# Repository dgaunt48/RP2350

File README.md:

# RP2350 - Various RP2350 Based Test Projects.

## DRAM_Tester
Code Based On https://github.com/schlae/pico-dram-tester.git
Vastly Cut Down. Just Learning How The RP2350 PIO Works.

## RP2350_LogicV6
50 x 50mm 4 layer self contained version of gusmanb's Logic Analyzer Version 6 Hardware.

## RP2350b_40GPIO
Simple RP2350b dev board with 40 level shifted gpio pins and 3 bit VGA output.

## RTC_MCP951X
Connect a MCP951X Spi Real Time Clock to the Raspberry Pi Pico.

## RTC_MSM6242B
Test the functionality of an obsolete MSM6242B Real Time Clock IC.

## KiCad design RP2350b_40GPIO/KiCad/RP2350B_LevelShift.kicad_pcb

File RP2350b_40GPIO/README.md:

# RP2350b_40GPIO
Simple RP2350b dev board with 40 level shifted gpio pins and 3 bit VGA output.

## Source\SelfTest_40GPIO
Plug a VGA cable in and bridge the left 20 IO pins to the RIGHT 20.
Self test will then perform a simple bi-directional check on all 40 pins, plus check for shorts against the two adjacent pins.
Not exhaustive but will catch most GPIO errors on the board.

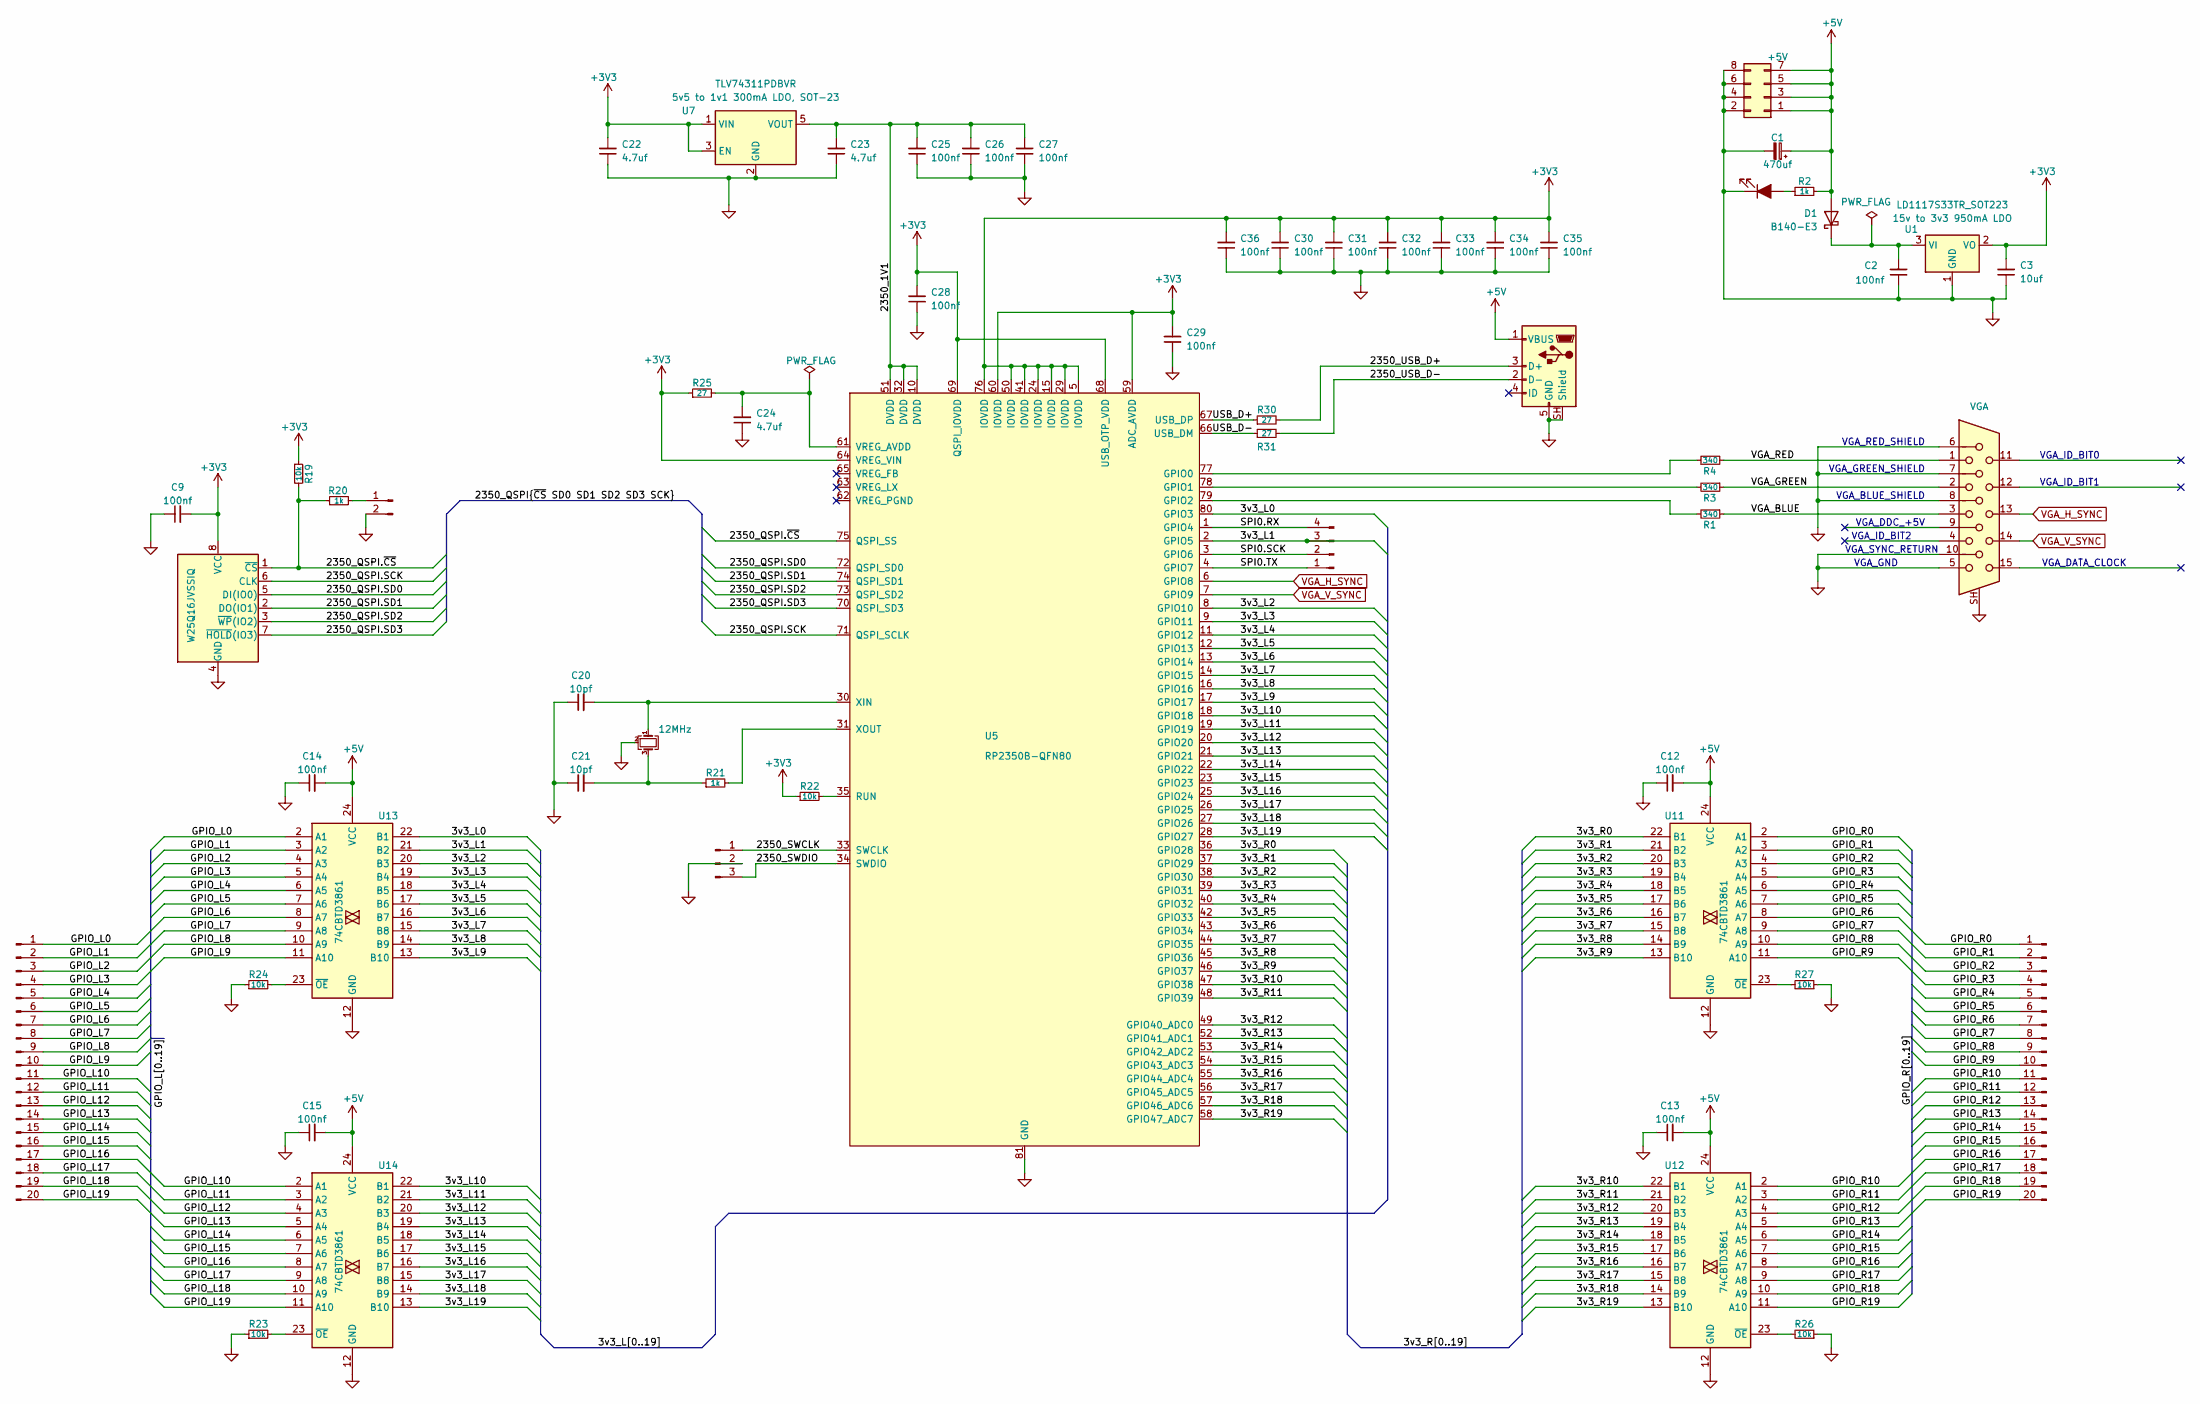
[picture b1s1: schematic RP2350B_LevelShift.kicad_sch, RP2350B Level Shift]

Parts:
C1: 470uf; CP_Radial_D5.0mm_P2.50mm
C2, C9, C12, C13, C14, C15, C25, C26, C27, C28, C29, C30, C31, C32, C33, C34, C35, C36: 100nf; C_0603_1608Metric
C3: 10uf; C_0805_2012Metric
C20, C21: 10pf; C_0603_1608Metric
C22, C23, C24: 4.7uf; C_0805_2012Metric
D1: B140-E3; D_SOD-123
J1: +5V; PinHeader_2x04_P2.54mm_Vertical
J2: Right GPIO; PinHeader_1x20_P2.54mm_Vertical
J3: VGA; 117345301
J4: Left GPIO; PinHeader_1x20_P2.54mm_Vertical
J7: SWD; PinHeader_1x03_P2.54mm_Vertical
J9: BOOT SEL; PinHeader_1x02_P2.54mm_Vertical
J10: SPI; PinHeader_1x04_P2.54mm_Vertical
J13: USB_B_Micro; USB_Micro-B_Amphenol_10103594-0001LF_Horizontal
Power1: POWER; LEDC2012X90N
R1, R3, R4: 340; R_0603_1608Metric
R2, R20, R21: 1k; R_0603_1608Metric
R19, R22, R23, R24, R26, R27: 10k; R_0603_1608Metric
R25, R30, R31: 27; R_0603_1608Metric
U1: LD1117S33TR_SOT223; SOT-223-3_TabPin2; Voltage 3v3
U2: W25Q16JVSSIQ; SOIC-8_5.23x5.23mm_P1.27mm
U5: RP2350B-QFN80; RP2350B_QFN-80_EP_10.573x10.573_Pitch0.4mm
U7: TLV74311PDBVR; SOT-23-5; Voltage 1v1
U11, U12, U13, U14: 74CBTD3861; SSOP-24_3.9x8.7mm_P0.635mm
Y1: 12MHz; Crystal_SMD_SeikoEpson_FA238V-4Pin_3.2x2.5mm

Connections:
+3V3: C3.2, C9.2, C22.2, C28.2, C29.2, C30.2, C31.2, C32.2, C33.2, C34.2, C35.2, C36.2, R19.1, R22.1, R25.1, U1.2 (VO), U2.8 (VCC), U5.5 (IOVDD), U5.15 (IOVDD), U5.24 (IOVDD), U5.29 (IOVDD), U5.41 (IOVDD), U5.50 (IOVDD), U5.59 (ADC_AVDD), U5.60 (IOVDD), U5.64 (VREG_VIN), U5.68 (USB_OTP_VDD), U5.69 (QSPI_IOVDD), U5.76 (IOVDD), U7.1 (VIN), U7.3 (EN)
+5V: C1.1, C12.2, C13.2, C14.2, C15.2, D1.2 (A), J1.1, J1.3, J1.5, J1.7, J13.1 (VBUS), R2.2, U11.24 (VCC), U12.24 (VCC), U13.24 (VCC), U14.24 (VCC)
/3v3_L0: U5.80 (GPIO3), U13.22 (B1)
/3v3_L1: J10.3, U5.2 (GPIO5), U13.21 (B2)
/3v3_L2: U5.8 (GPIO10), U13.20 (B3)
/3v3_L3: U5.9 (GPIO11), U13.19 (B4)
/3v3_L4: U5.11 (GPIO12), U13.18 (B5)
/3v3_L5: U5.12 (GPIO13), U13.17 (B6)
/3v3_L6: U5.13 (GPIO14), U13.16 (B7)
/3v3_L7: U5.14 (GPIO15), U13.15 (B8)
/3v3_L8: U5.16 (GPIO16), U13.14 (B9)
/3v3_L9: U5.17 (GPIO17), U13.13 (B10)
/3v3_L10: U5.18 (GPIO18), U14.22 (B1)
/3v3_L11: U5.19 (GPIO19), U14.21 (B2)
/3v3_L12: U5.20 (GPIO20), U14.20 (B3)
/3v3_L13: U5.21 (GPIO21), U14.19 (B4)
/3v3_L14: U5.22 (GPIO22), U14.18 (B5)
/3v3_L15: U5.23 (GPIO23), U14.17 (B6)
/3v3_L16: U5.25 (GPIO24), U14.16 (B7)
/3v3_L17: U5.26 (GPIO25), U14.15 (B8)
/3v3_L18: U5.27 (GPIO26), U14.14 (B9)
/3v3_L19: U5.28 (GPIO27), U14.13 (B10)
/3v3_R0: U5.36 (GPIO28), U11.22 (B1)
/3v3_R1: U5.37 (GPIO29), U11.21 (B2)
/3v3_R2: U5.38 (GPIO30), U11.20 (B3)
/3v3_R3: U5.39 (GPIO31), U11.19 (B4)
/3v3_R4: U5.40 (GPIO32), U11.18 (B5)
/3v3_R5: U5.42 (GPIO33), U11.17 (B6)
/3v3_R6: U5.43 (GPIO34), U11.16 (B7)
/3v3_R7: U5.44 (GPIO35), U11.15 (B8)
/3v3_R8: U5.45 (GPIO36), U11.14 (B9)
/3v3_R9: U5.46 (GPIO37), U11.13 (B10)
/3v3_R10: U5.47 (GPIO38), U12.22 (B1)
/3v3_R11: U5.48 (GPIO39), U12.21 (B2)
/3v3_R12: U5.49 (GPIO40_ADC0), U12.20 (B3)
/3v3_R13: U5.52 (GPIO41_ADC1), U12.19 (B4)
/3v3_R14: U5.53 (GPIO42_ADC2), U12.18 (B5)
/3v3_R15: U5.54 (GPIO43_ADC3), U12.17 (B6)
/3v3_R16: U5.55 (GPIO44_ADC4), U12.16 (B7)
/3v3_R17: U5.56 (GPIO45_ADC5), U12.15 (B8)
/3v3_R18: U5.57 (GPIO46_ADC6), U12.14 (B9)
/3v3_R19: U5.58 (GPIO47_ADC7), U12.13 (B10)
/2350_1V1: C23.2, C25.2, C26.2, C27.2, U5.10 (DVDD), U5.32 (DVDD), U5.51 (DVDD), U7.5 (VOUT)
/2350_QSPI.SCK: U2.6 (CLK), U5.71 (QSPI_SCLK)
/2350_QSPI.SD0: U2.5 (DI(IO0)), U5.72 (QSPI_SD0)
/2350_QSPI.SD1: U2.2 (DO(IO1)), U5.74 (QSPI_SD1)
/2350_QSPI.SD2: U2.3 (~WP(IO2)), U5.73 (QSPI_SD2)
/2350_QSPI.SD3: U2.7 (~HOLD(IO3)), U5.70 (QSPI_SD3)
/2350_QSPI.~CS: R19.2, R20.1, U2.1 (~CS), U5.75 (QSPI_SS)
/2350_SWCLK: J7.1, U5.33 (SWCLK)
/2350_SWDIO: J7.3, U5.34 (SWDIO)
/2350_USB_D+: J13.3 (D+), R30.2
/2350_USB_D-: J13.2 (D-), R31.2
/GPIO_L0: J4.1, U13.2 (A1)
/GPIO_L1: J4.2, U13.3 (A2)
/GPIO_L2: J4.3, U13.4 (A3)
/GPIO_L3: J4.4, U13.5 (A4)
/GPIO_L4: J4.5, U13.6 (A5)
/GPIO_L5: J4.6, U13.7 (A6)
/GPIO_L6: J4.7, U13.8 (A7)
/GPIO_L7: J4.8, U13.9 (A8)
/GPIO_L8: J4.9, U13.10 (A9)
/GPIO_L9: J4.10, U13.11 (A10)
/GPIO_L10: J4.11, U14.2 (A1)
/GPIO_L11: J4.12, U14.3 (A2)
/GPIO_L12: J4.13, U14.4 (A3)
/GPIO_L13: J4.14, U14.5 (A4)
/GPIO_L14: J4.15, U14.6 (A5)
/GPIO_L15: J4.16, U14.7 (A6)
/GPIO_L16: J4.17, U14.8 (A7)
/GPIO_L17: J4.18, U14.9 (A8)
/GPIO_L18: J4.19, U14.10 (A9)
/GPIO_L19: J4.20, U14.11 (A10)
/GPIO_R0: J2.1, U11.2 (A1)
/GPIO_R1: J2.2, U11.3 (A2)
/GPIO_R2: J2.3, U11.4 (A3)
/GPIO_R3: J2.4, U11.5 (A4)
/GPIO_R4: J2.5, U11.6 (A5)
/GPIO_R5: J2.6, U11.7 (A6)
/GPIO_R6: J2.7, U11.8 (A7)
/GPIO_R7: J2.8, U11.9 (A8)
/GPIO_R8: J2.9, U11.10 (A9)
/GPIO_R9: J2.10, U11.11 (A10)
/GPIO_R10: J2.11, U12.2 (A1)
/GPIO_R11: J2.12, U12.3 (A2)
/GPIO_R12: J2.13, U12.4 (A3)
/GPIO_R13: J2.14, U12.5 (A4)
/GPIO_R14: J2.15, U12.6 (A5)
/GPIO_R15: J2.16, U12.7 (A6)
/GPIO_R16: J2.17, U12.8 (A7)
/GPIO_R17: J2.18, U12.9 (A8)
/GPIO_R18: J2.19, U12.10 (A9)
/GPIO_R19: J2.20, U12.11 (A10)
/SPI0.RX: J10.4, U5.1 (GPIO4)
/SPI0.SCK: J10.2, U5.3 (GPIO6)
/SPI0.TX: J10.1, U5.4 (GPIO7)
/USB_D+: R30.1, U5.67 (USB_DP)
/USB_D-: R31.1, U5.66 (USB_DM)
/VGA_BLUE: J3.3, R1.1
/VGA_GREEN: J3.2, R3.1
/VGA_RED: J3.1, R4.1
GND: C1.2, C2.1, C3.1, C9.1, C12.1, C13.1, C14.1, C15.1, C20.1, C21.1, C22.1, C23.1, C24.1, C25.1, C26.1, C27.1, C28.1, C29.1, C30.1, C31.1, C32.1, C33.1, C34.1, C35.1, C36.1, J1.2, J1.4, J1.6, J1.8, J3.5, J3.6, J3.7, J3.8, J3.10, J3.SH, J7.2, J9.2, J13.5 (GND), J13.SH (Shield), Power1.1 (K), R23.1, R24.1, R26.1, R27.1, U1.1 (GND), U2.4 (GND), U5.81 (GND), U7.2 (GND), U11.12 (GND), U12.12 (GND), U13.12 (GND), U14.12 (GND), Y1.2 (G), Y1.4 (G)
unnamed: C21.2, R21.1, Y1.3
unnamed: C2.2, D1.1 (K), U1.3 (VI)
unnamed: J9.1, R20.2
unnamed: Power1.2 (A), R2.1
unnamed: R4.2, U5.77 (GPIO0)
unnamed: R3.2, U5.78 (GPIO1)
unnamed: R1.2, U5.79 (GPIO2)
unnamed: R22.2, U5.35 (RUN)
unnamed: C24.2, R25.2, U5.61 (VREG_AVDD)
unnamed: C20.2, U5.30 (XIN), Y1.1
unnamed: R21.2, U5.31 (XOUT)
unnamed: R27.2, U11.23 (~OE)
unnamed: R26.2, U12.23 (~OE)
unnamed: R24.2, U13.23 (~OE)
unnamed: R23.2, U14.23 (~OE)
VGA_H_SYNC: J3.13, U5.6 (GPIO8)
VGA_V_SYNC: J3.14, U5.7 (GPIO9)

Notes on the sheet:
VGA_ID_BIT2
VGA_ID_BIT1
VGA_BLUE_SHIELD
VGA_ID_BIT0
VGA_DATA_CLOCK
VGA_RED_SHIELD
VGA_DDC_+5V
VGA_SYNC_RETURN
VGA_GND
VGA_GREEN_SHIELD

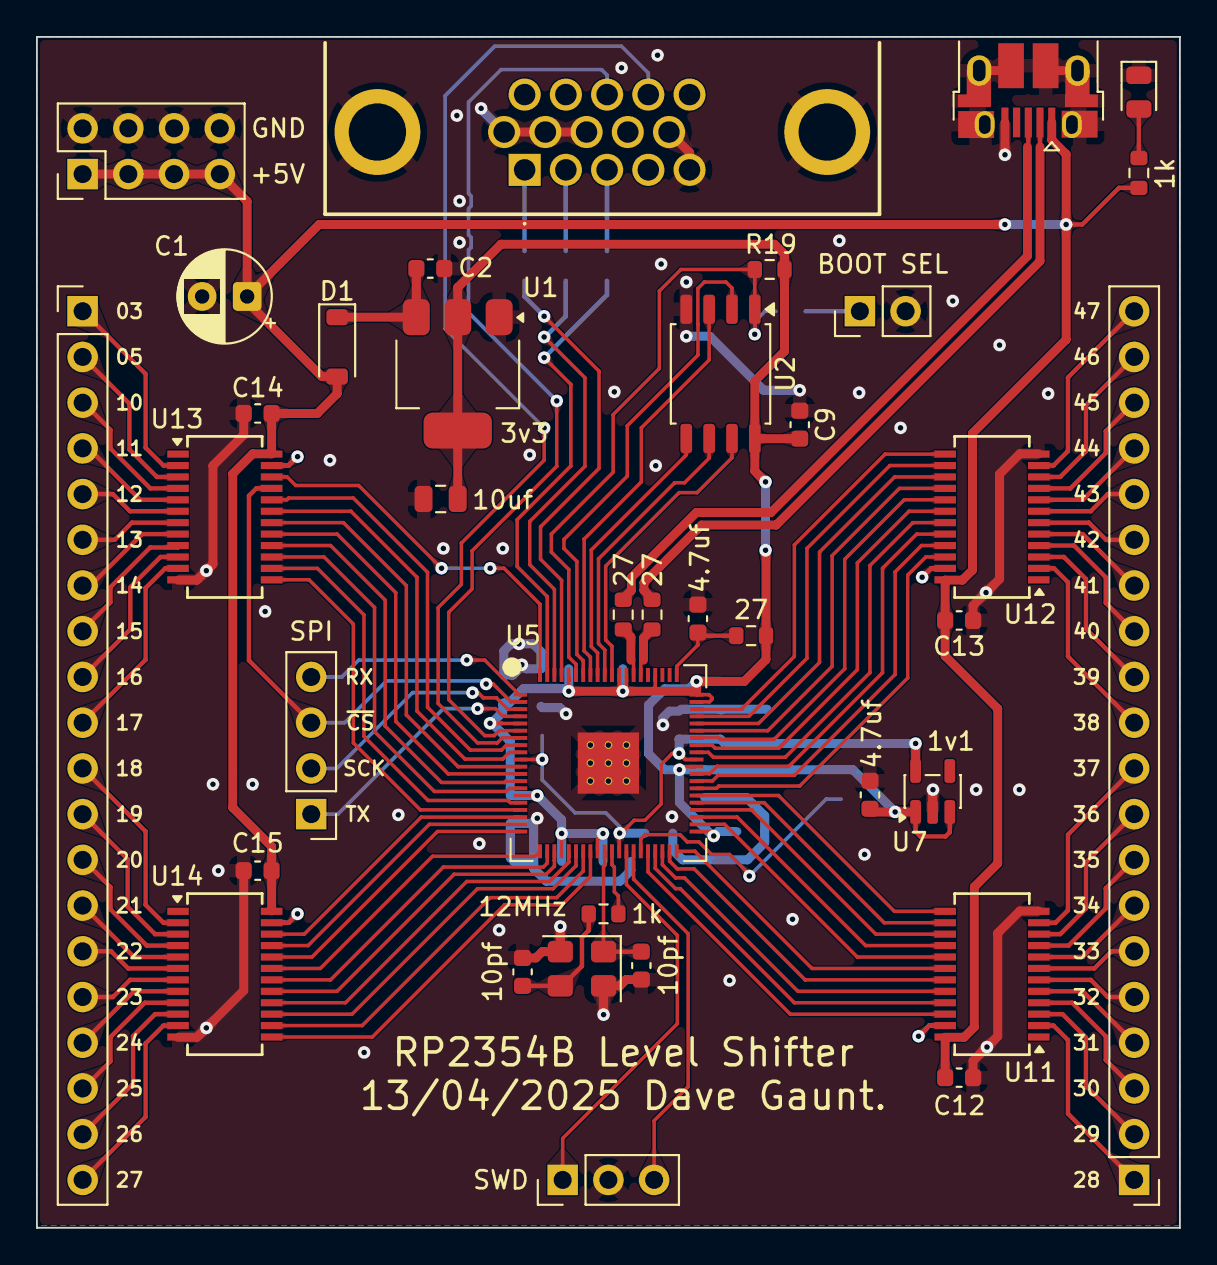
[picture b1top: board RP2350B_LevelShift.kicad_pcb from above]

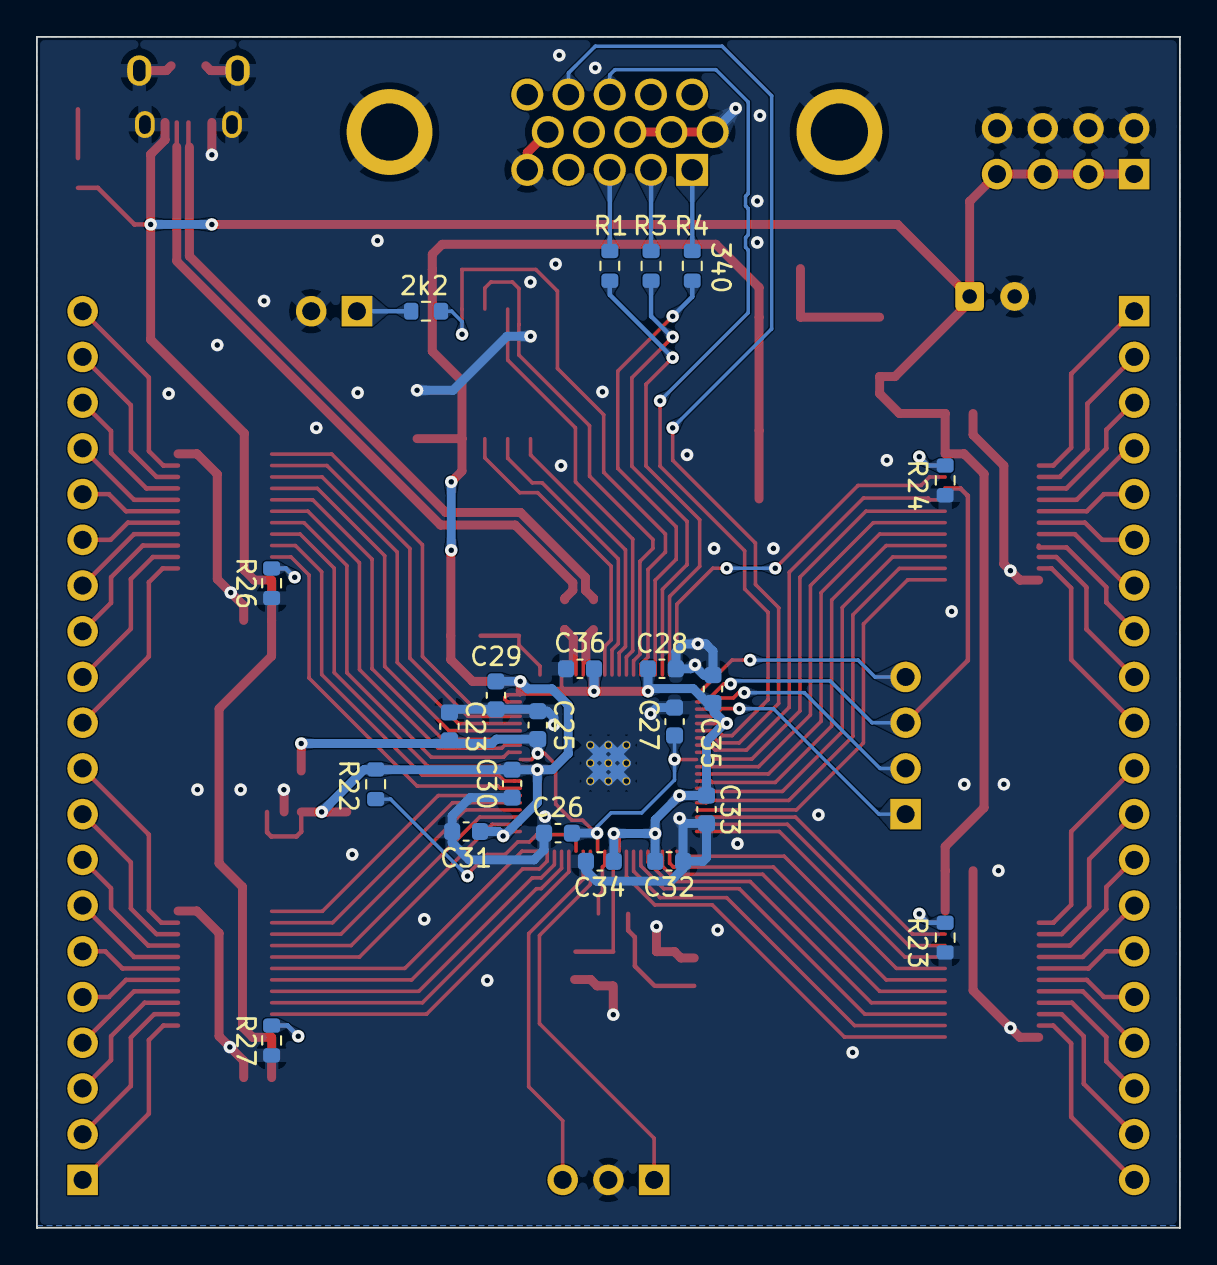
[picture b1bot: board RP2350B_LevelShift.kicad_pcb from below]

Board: 2 copper layers, 63.5 x 66.2 mm, 59 parts (22 on the bottom side), 119 nets.

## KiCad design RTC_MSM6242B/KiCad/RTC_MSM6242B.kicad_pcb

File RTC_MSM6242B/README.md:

# MSM6242B Real Time Clock

Project to test the functionality of an obsolete MSM6242B Real Time Clock IC with the 2350.

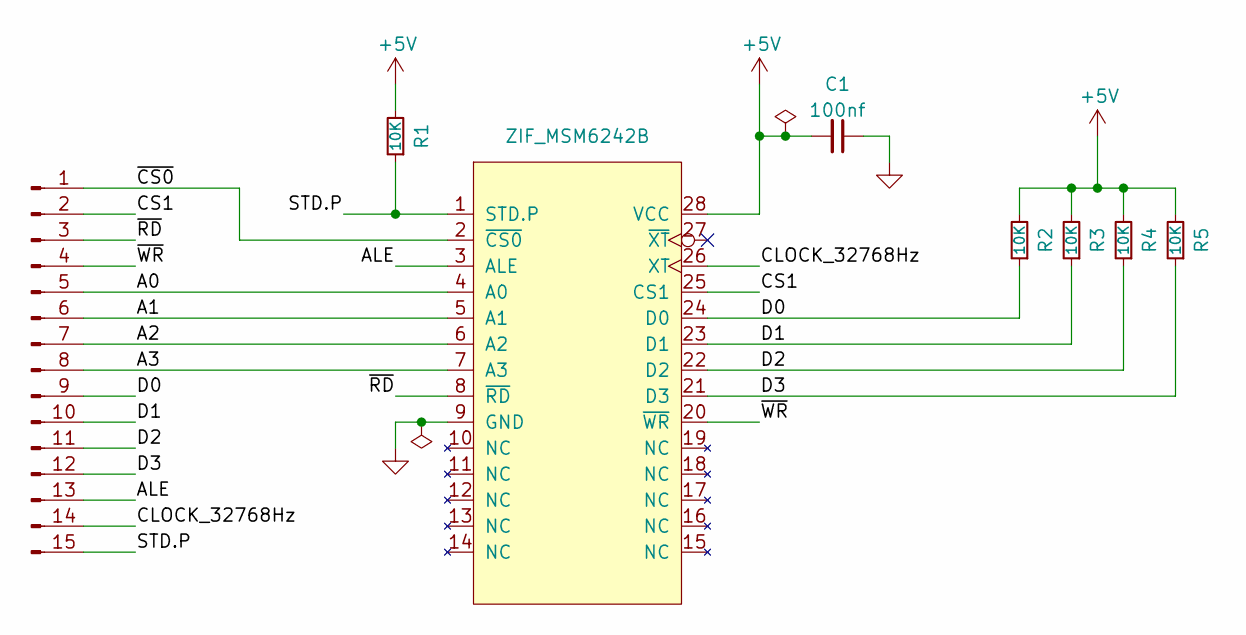
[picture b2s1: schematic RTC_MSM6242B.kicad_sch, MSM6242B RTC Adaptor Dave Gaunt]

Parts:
C1: 100nf; C_0603_1608Metric
J1: PinHeader_1x15_P2.54mm_Vertical
R1, R2, R3, R4, R5: 10K; R_0603_1608Metric
U1: ZIF_MSM6242B; ZIF-28_W11.9mm_W12.7mm_W15.24mm_W17.78mm_W18.5mm_3M_228-127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

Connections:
+5V: C1.2, R1.2, R2.2, R3.2, R4.2, R5.2, U1.28 (VCC)
/A0: J1.5, U1.4 (A0)
/A1: J1.6, U1.5 (A1)
/A2: J1.7, U1.6 (A2)
/A3: J1.8, U1.7 (A3)
/ALE: J1.13, U1.3 (ALE)
/CLOCK_32768Hz: J1.14, U1.26 (XT)
/CS1: J1.2, U1.25 (CS1)
/D0: J1.9, R2.1, U1.24 (D0)
/D1: J1.10, R3.1, U1.23 (D1)
/D2: J1.11, R4.1, U1.22 (D2)
/D3: J1.12, R5.1, U1.21 (D3)
/STD.P: J1.15, R1.1, U1.1 (STD.P)
/~CS0: J1.1, U1.2 (~CS0)
/~RD: J1.3, U1.8 (~RD)
/~WR: J1.4, U1.20 (~WR)
GND: C1.1, U1.9 (GND)

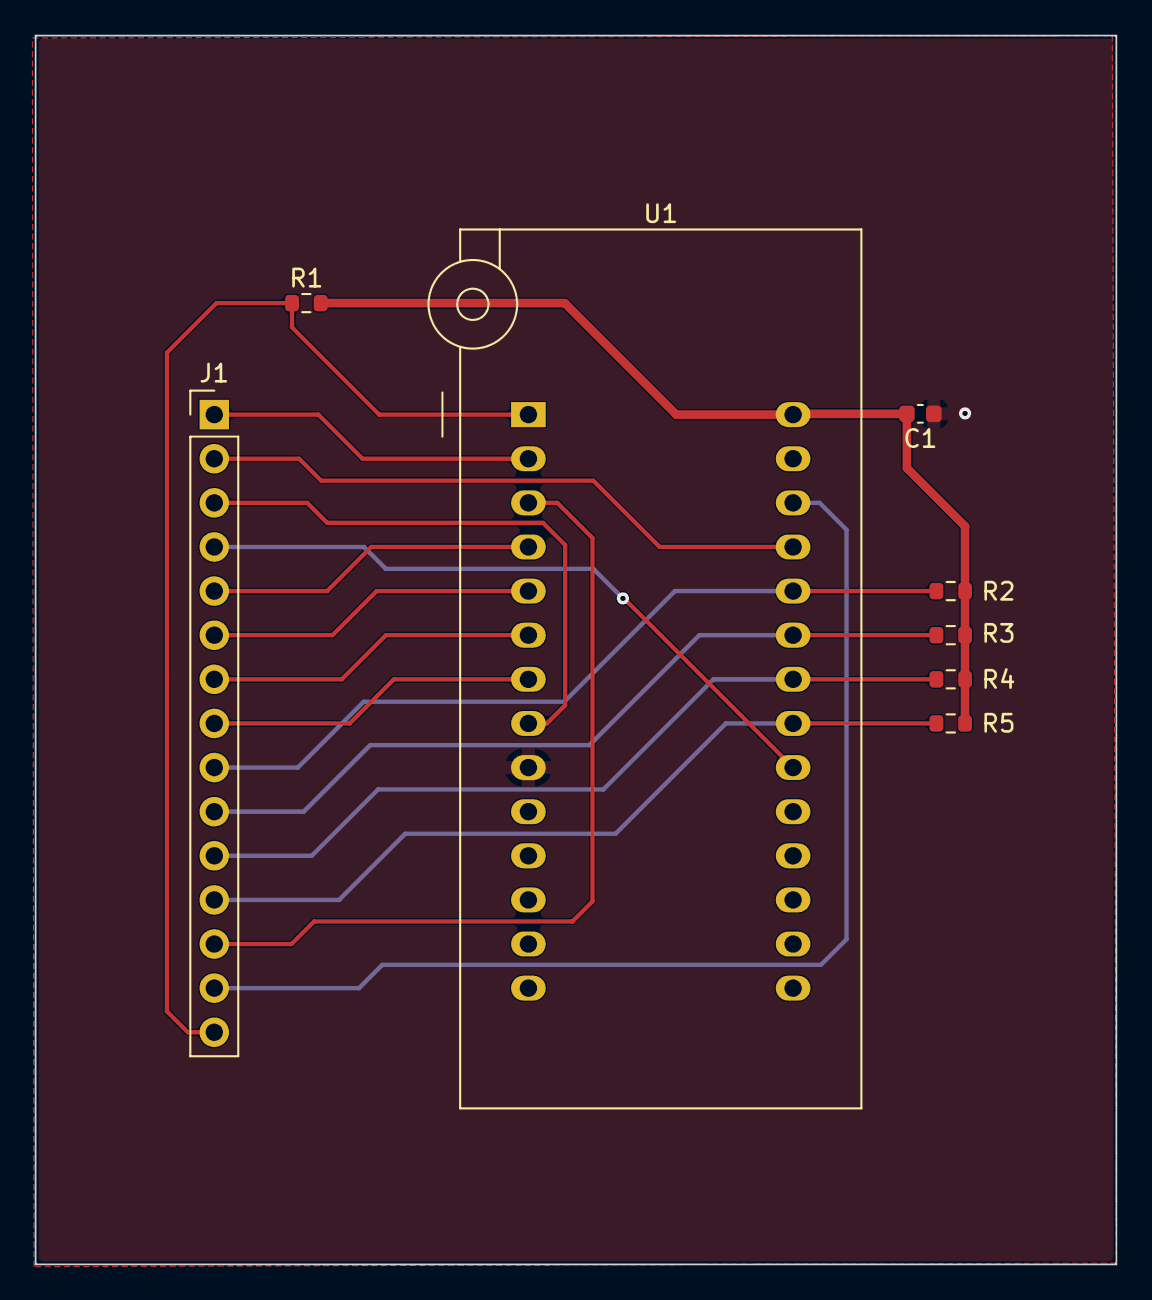
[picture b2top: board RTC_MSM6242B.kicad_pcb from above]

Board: 2 copper layers, 62.2 x 70.7 mm, 8 parts (0 on the bottom side), 17 nets.

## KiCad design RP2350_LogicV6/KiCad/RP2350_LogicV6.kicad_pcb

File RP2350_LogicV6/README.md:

# RP2350_LogicV6

50 x 50mm 4 layer self contained version of gusmanb's Logic Analyzer Hardware.

https://github.com/gusmanb/logicanalyzer.git

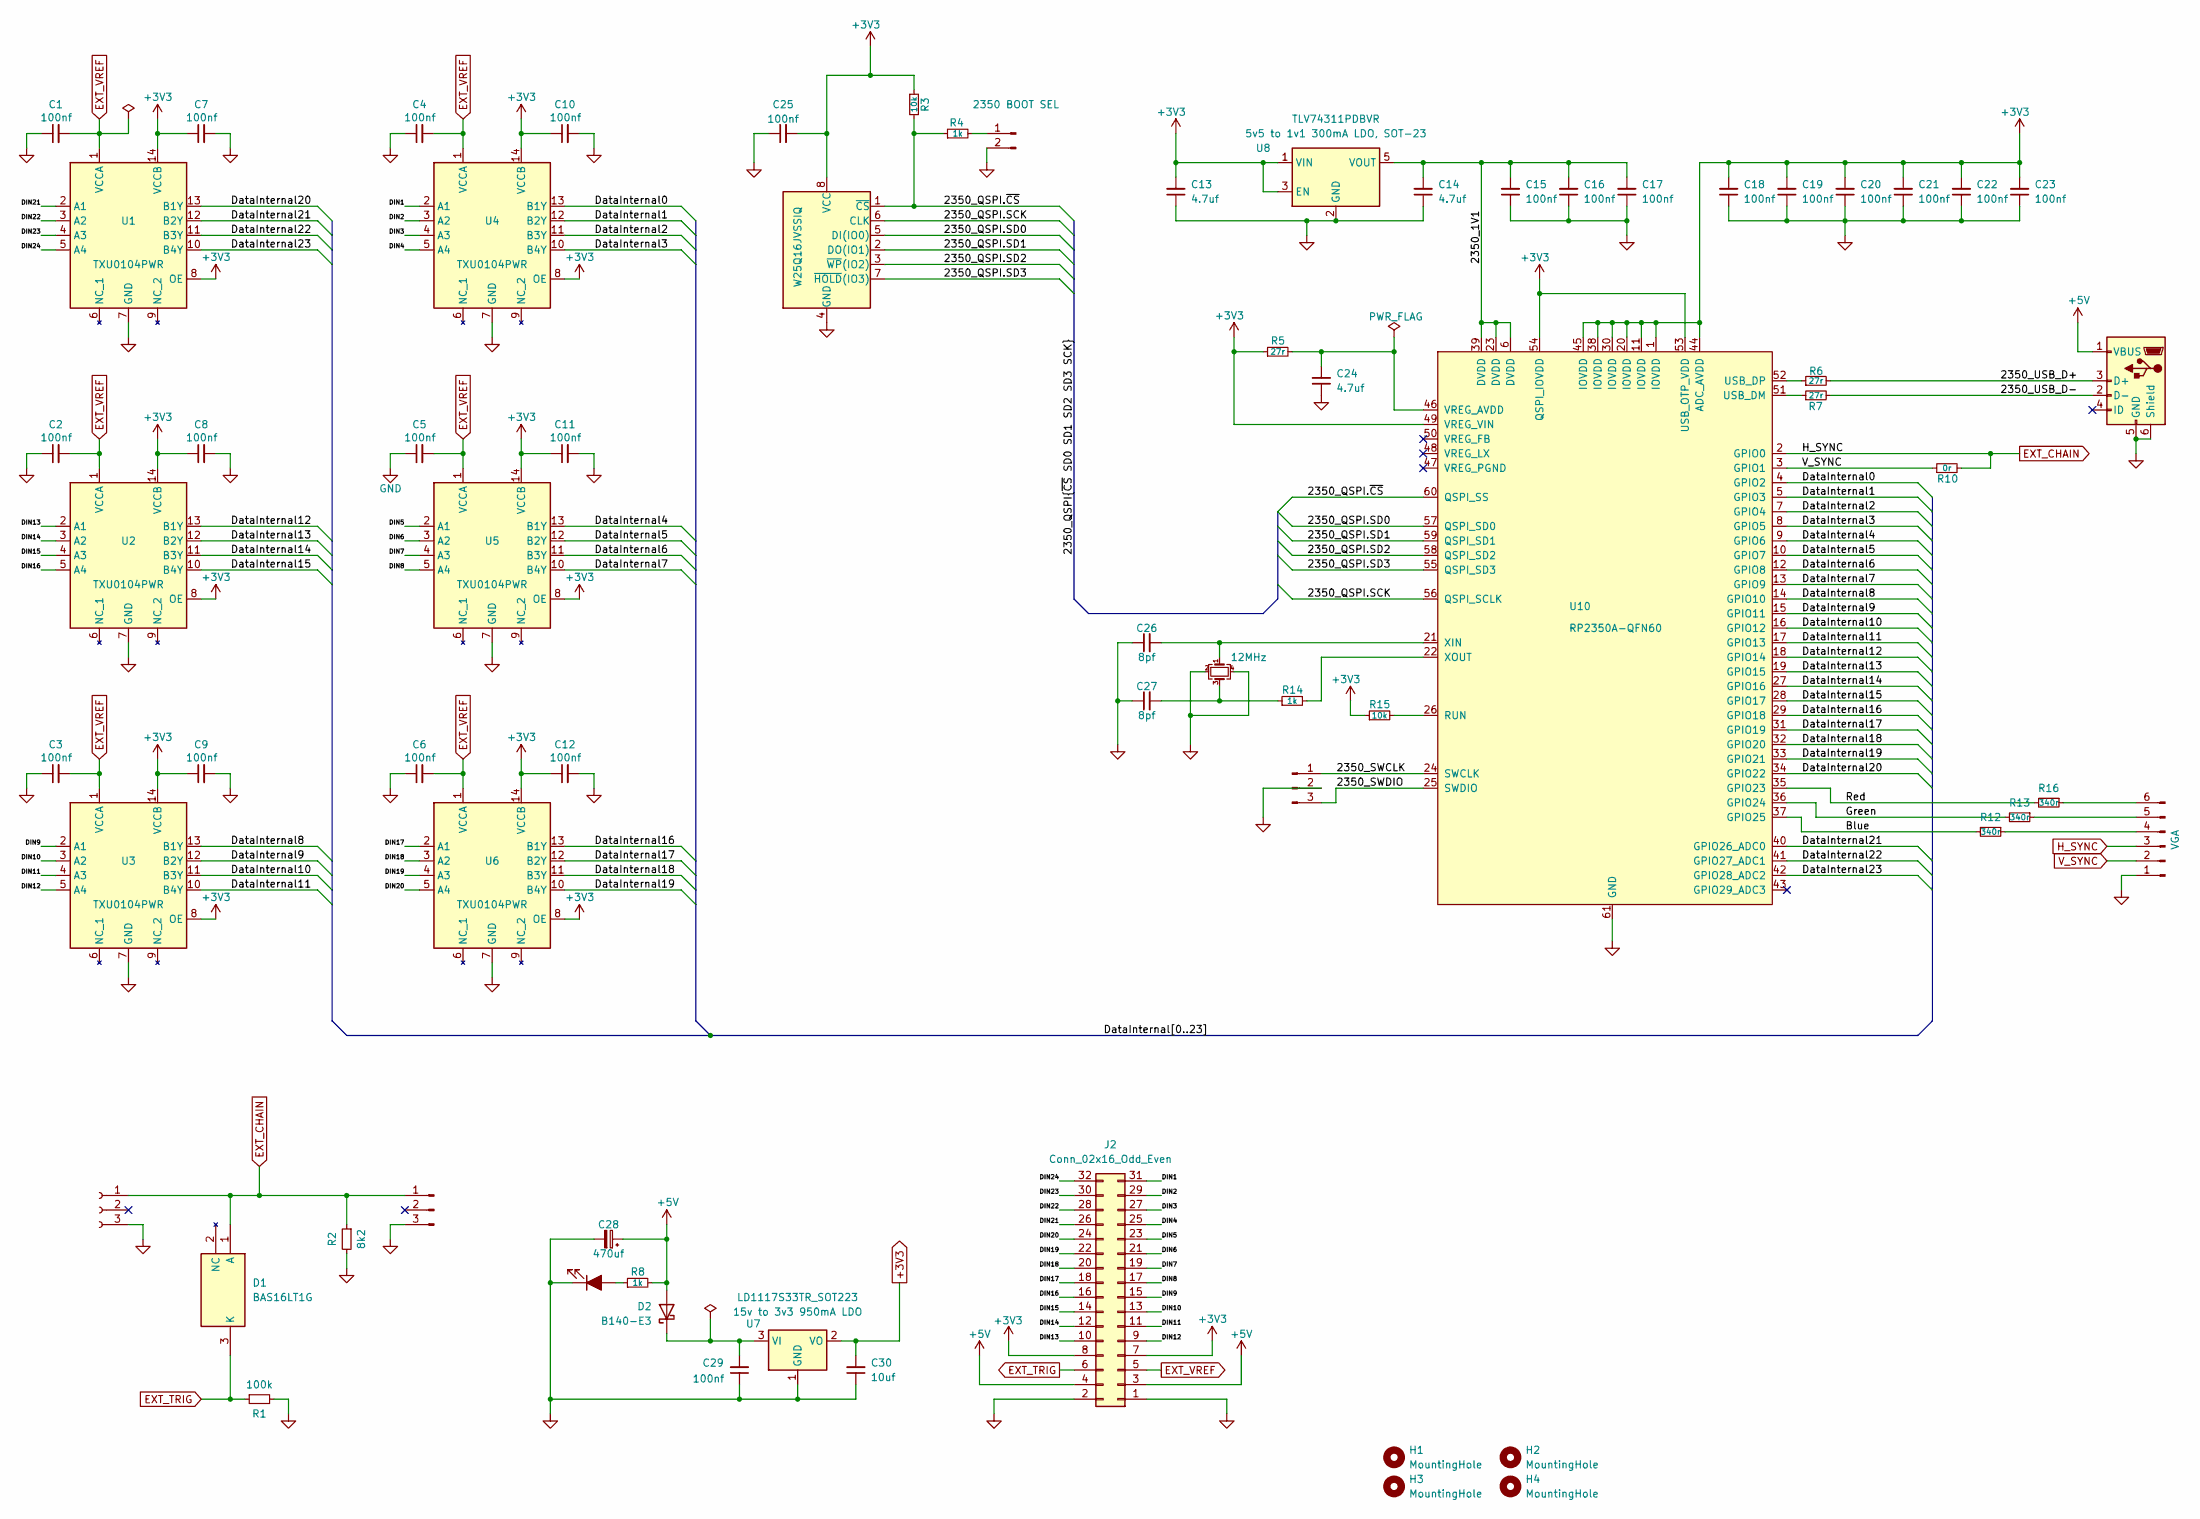
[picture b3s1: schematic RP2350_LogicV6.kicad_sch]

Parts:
C1, C2, C3, C4, C5, C6, C7, C8, C9, C10, C11, C12, C15, C16, C17, C18, C19, C20, C21, C22, C23, C25, C29: 100nf; C_0603_1608Metric
C13, C14, C24: 4.7uf; C_0805_2012Metric
C26, C27: 8pf; C_0603_1608Metric
C28: 470uf; CP_Radial_D5.0mm_P2.50mm
C30: 10uf; C_0805_2012Metric
D1: BAS16LT1G; SOT96P237X111-3N; Mouser Part Number 863-BAS16LT1G
D2: B140-E3; D_SOD-123
H1, H2, H3, H4: MountingHole; MountingHole_2.5mm
J2: Conn_02x16_Odd_Even; PinHeader_2x16_P2.54mm_Horizontal
J3: SWD; PinSocket_1x03_P2.54mm_Horizontal
J4: USB_B_Micro; USB_Micro-B_Amphenol_10103594-0001LF_Horizontal
J5: 2350 BOOT SEL; PinHeader_1x02_P2.54mm_Vertical
J6: SWD; PinHeader_1x03_P2.54mm_Vertical
J7: SWD; PinHeader_1x03_P2.54mm_Horizontal
J9: VGA; PinHeader_1x06_P2.54mm_Vertical
Power1: POWER; LEDC2012X90N
R1: 100k; R_0603_1608Metric
R2: 8k2; R_0603_1608Metric
R3, R15: 10k; R_0603_1608Metric
R4, R8, R14: 1k; R_0603_1608Metric
R5, R6, R7: 27r; R_0603_1608Metric
R10: 0r; R_0603_1608Metric
R12, R13, R16: 340r; R_0603_1608Metric
U1, U2, U3, U4, U5, U6: TXU0104PWR; SOP65P640X120-14N; Mouser Part Number 595-TXU0104PWR
U7: LD1117S33TR_SOT223; SOT-223-3_TabPin2; Voltage 3v3
U8: TLV74311PDBVR; SOT-23-5; Voltage 1v1
U9: W25Q16JVSSIQ; SOIC-8_5.23x5.23mm_P1.27mm
U10: RP2350A-QFN60; RP2350A_QFN-60_EP_7.75x7.75_Pitch0.4mm
Y1: 12MHz; Crystal_SMD_SeikoEpson_FA238V-4Pin_3.2x2.5mm

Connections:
+3V3: C7.1, C8.1, C9.1, C10.1, C11.1, C12.1, C13.2, C18.2, C19.2, C20.2, C21.2, C22.2, C23.2, C25.2, C30.2, J2.7, J2.8, R3.1, R5.1, R15.1, U1.8 (OE), U1.14 (VCCB), U2.8 (OE), U2.14 (VCCB), U3.8 (OE), U3.14 (VCCB), U4.8 (OE), U4.14 (VCCB), U5.8 (OE), U5.14 (VCCB), U6.8 (OE), U6.14 (VCCB), U7.2 (VO), U8.1 (VIN), U8.3 (EN), U9.8 (VCC), U10.1 (IOVDD), U10.11 (IOVDD), U10.20 (IOVDD), U10.30 (IOVDD), U10.38 (IOVDD), U10.44 (ADC_AVDD), U10.45 (IOVDD), U10.49 (VREG_VIN), U10.53 (USB_OTP_VDD), U10.54 (QSPI_IOVDD)
+5V: C28.1, D2.2 (A), J2.3, J2.4, J4.1 (VBUS), R8.2
/2350_1V1: C14.2, C15.2, C16.2, C17.2, U8.5 (VOUT), U10.6 (DVDD), U10.23 (DVDD), U10.39 (DVDD)
/2350_QSPI.SCK: U9.6 (CLK), U10.56 (QSPI_SCLK)
/2350_QSPI.SD0: U9.5 (DI(IO0)), U10.57 (QSPI_SD0)
/2350_QSPI.SD1: U9.2 (DO(IO1)), U10.59 (QSPI_SD1)
/2350_QSPI.SD2: U9.3 (~WP(IO2)), U10.58 (QSPI_SD2)
/2350_QSPI.SD3: U9.7 (~HOLD(IO3)), U10.55 (QSPI_SD3)
/2350_QSPI.~CS: R3.2, R4.1, U9.1 (~CS), U10.60 (QSPI_SS)
/2350_SWCLK: J6.1, U10.24 (SWCLK)
/2350_SWDIO: J6.3, U10.25 (SWDIO)
/2350_USB_D+: J4.3 (D+), R6.2
/2350_USB_D-: J4.2 (D-), R7.2
/Blue: R12.2, U10.37 (GPIO25)
/DIN1: J2.31, U4.2 (A1)
/DIN2: J2.29, U4.3 (A2)
/DIN3: J2.27, U4.4 (A3)
/DIN4: J2.25, U4.5 (A4)
/DIN5: J2.23, U5.2 (A1)
/DIN6: J2.21, U5.3 (A2)
/DIN7: J2.19, U5.4 (A3)
/DIN8: J2.17, U5.5 (A4)
/DIN9: J2.15, U3.2 (A1)
/DIN10: J2.13, U3.3 (A2)
/DIN11: J2.11, U3.4 (A3)
/DIN12: J2.9, U3.5 (A4)
/DIN13: J2.10, U2.2 (A1)
/DIN14: J2.12, U2.3 (A2)
/DIN15: J2.14, U2.4 (A3)
/DIN16: J2.16, U2.5 (A4)
/DIN17: J2.18, U6.2 (A1)
/DIN18: J2.20, U6.3 (A2)
/DIN19: J2.22, U6.4 (A3)
/DIN20: J2.24, U6.5 (A4)
/DIN21: J2.26, U1.2 (A1)
/DIN22: J2.28, U1.3 (A2)
/DIN23: J2.30, U1.4 (A3)
/DIN24: J2.32, U1.5 (A4)
/DataInternal0: U4.13 (B1Y), U10.4 (GPIO2)
/DataInternal1: U4.12 (B2Y), U10.5 (GPIO3)
/DataInternal2: U4.11 (B3Y), U10.7 (GPIO4)
/DataInternal3: U4.10 (B4Y), U10.8 (GPIO5)
/DataInternal4: U5.13 (B1Y), U10.9 (GPIO6)
/DataInternal5: U5.12 (B2Y), U10.10 (GPIO7)
/DataInternal6: U5.11 (B3Y), U10.12 (GPIO8)
/DataInternal7: U5.10 (B4Y), U10.13 (GPIO9)
/DataInternal8: U3.13 (B1Y), U10.14 (GPIO10)
/DataInternal9: U3.12 (B2Y), U10.15 (GPIO11)
/DataInternal10: U3.11 (B3Y), U10.16 (GPIO12)
/DataInternal11: U3.10 (B4Y), U10.17 (GPIO13)
/DataInternal12: U2.13 (B1Y), U10.18 (GPIO14)
/DataInternal13: U2.12 (B2Y), U10.19 (GPIO15)
/DataInternal14: U2.11 (B3Y), U10.27 (GPIO16)
/DataInternal15: U2.10 (B4Y), U10.28 (GPIO17)
/DataInternal16: U6.13 (B1Y), U10.29 (GPIO18)
/DataInternal17: U6.12 (B2Y), U10.31 (GPIO19)
/DataInternal18: U6.11 (B3Y), U10.32 (GPIO20)
/DataInternal19: U6.10 (B4Y), U10.33 (GPIO21)
/DataInternal20: U1.13 (B1Y), U10.34 (GPIO22)
/DataInternal21: U1.12 (B2Y), U10.40 (GPIO26_ADC0)
/DataInternal22: U1.11 (B3Y), U10.41 (GPIO27_ADC1)
/DataInternal23: U1.10 (B4Y), U10.42 (GPIO28_ADC2)
/Green: R13.2, U10.36 (GPIO24)
/Red: R16.2, U10.35 (GPIO23)
/V_SYNC: J9.2, R10.1, U10.3 (GPIO1)
EXT_TRIG: D1.3 (K), J2.6, R1.1
EXT_VREF: C1.2, C2.2, C3.2, C4.2, C5.2, C6.2, J2.5, U1.1 (VCCA), U2.1 (VCCA), U3.1 (VCCA), U4.1 (VCCA), U5.1 (VCCA), U6.1 (VCCA)
GND: C1.1, C2.1, C3.1, C4.1, C5.1, C6.1, C7.2, C8.2, C9.2, C10.2, C11.2, C12.2, C13.1, C14.1, C15.1, C16.1, C17.1, C18.1, C19.1, C20.1, C21.1, C22.1, C23.1, C24.1, C25.1, C26.1, C27.1, C28.2, C29.1, C30.1, J2.1, J2.2, J3.3, J4.5 (GND), J4.6 (Shield), J4.SH (Shield), J5.2, J6.2, J7.3, J9.1, Power1.1 (K), R1.2, R2.2, U1.7 (GND), U2.7 (GND), U3.7 (GND), U4.7 (GND), U5.7 (GND), U6.7 (GND), U7.1 (GND), U8.2 (GND), U9.4 (GND), U10.61 (GND), Y1.2 (G), Y1.4 (G)
unnamed: C27.2, R14.1, Y1.3
unnamed: C29.2, D2.1 (K), U7.3 (VI)
unnamed: J5.1, R4.2
unnamed: J9.4, R12.1
unnamed: J9.5, R13.1
unnamed: J9.6, R16.1
unnamed: Power1.2 (A), R8.1
unnamed: R15.2, U10.26 (RUN)
unnamed: R7.1, U10.51 (USB_DM)
unnamed: R6.1, U10.52 (USB_DP)
unnamed: C24.2, R5.2, U10.46 (VREG_AVDD)
unnamed: C26.2, U10.21 (XIN), Y1.1
unnamed: R14.2, U10.22 (XOUT)

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
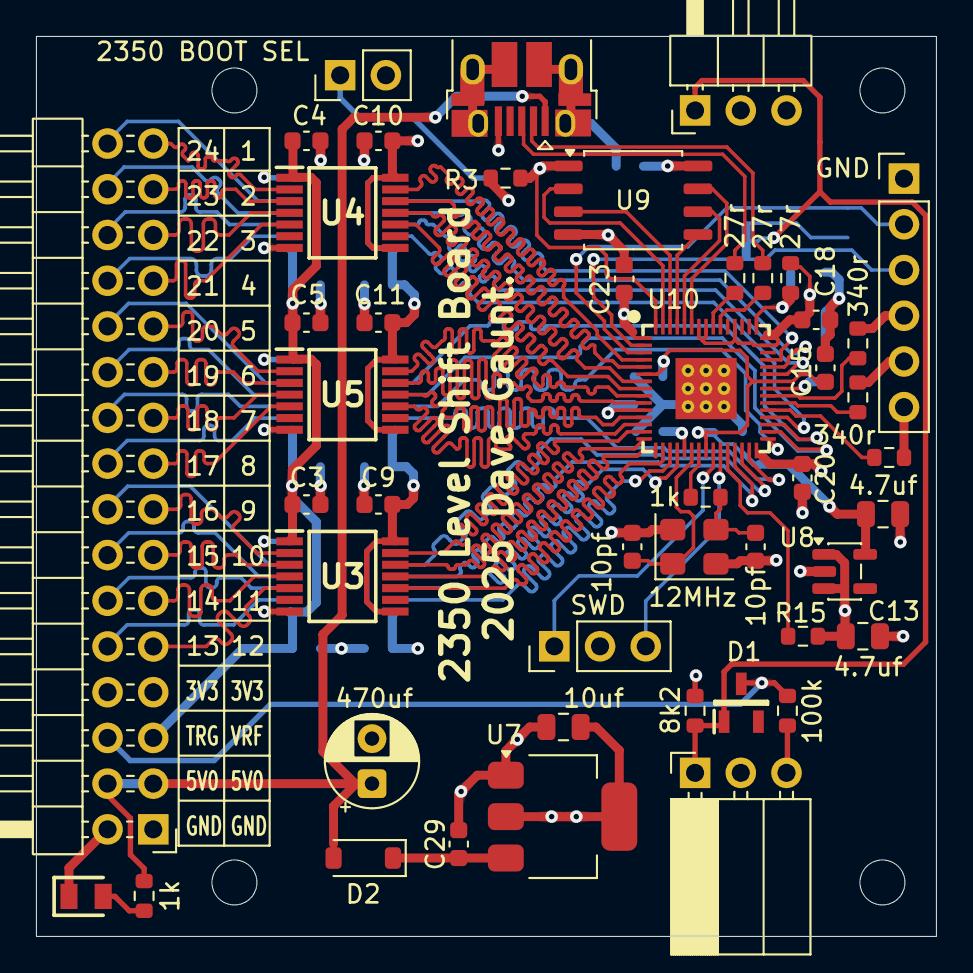
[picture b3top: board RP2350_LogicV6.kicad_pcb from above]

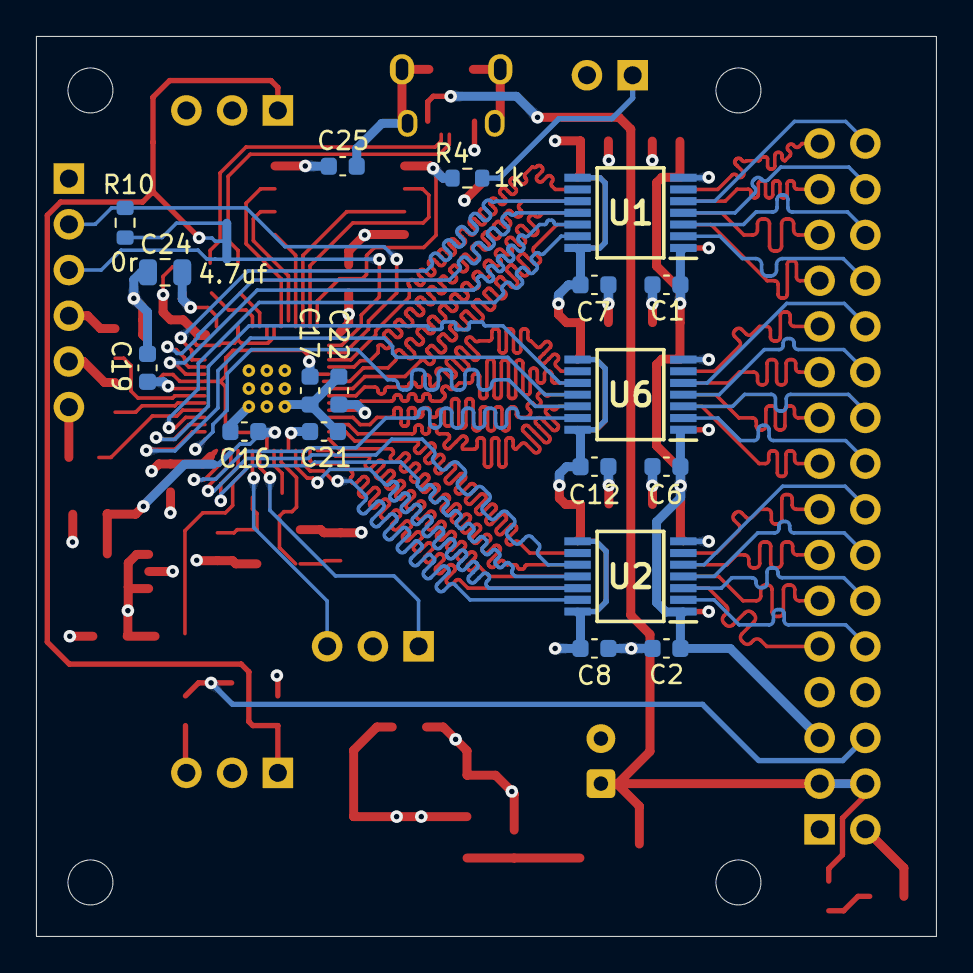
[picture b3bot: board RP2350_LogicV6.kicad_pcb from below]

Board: 4 copper layers, 50.0 x 50.0 mm, 70 parts (19 on the bottom side), 84 nets.

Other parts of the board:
NT1: NetTie_3; NetTie-3_SMD_Pad0.5mm

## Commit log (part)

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2026-02-13 - Initial Commit
2026-02-22 - VIA Timer Is Blinking The VIC20 Cursor.
2026-02-26 - Added support for IO Port A and B, Sort of reads the VIC20 keyboard but has timing issues.
2026-02-28 - Created the project.
2026-02-28 - Added code to display all VIA registers.
2026-02-28 - Signals onPort A & B are now displayed on the VGA output.
2026-02-28 - Moved Some Files I Use All The Time To A Common Directory.
2026-02-28 - VIC20 Keyboard is mostly working. There is an occasional timing error if you hold a key down. It will sometimes generate the wrong key code, mostly noticable on the shift and ctrl keys.
2026-02-28 - VIA is running well enough to type on the VIC 20 keyboard now.
2026-04-02 - Added the common VGA functions I use all the time.
2026-04-02 - Added u16 endian swap to types.h
2026-04-03 - Updated To KiCad 10.0
2026-04-03 - Added driver code for the AdaFruit 4383 lcd.
2026-04-03 - New Project Files.
2026-04-04 - Just did a really simple test of the first 100 bits of a 4164 DRAM IC.
2026-04-26 - Updated to KiCad 10
2026-04-26 - Moved SpiNorFlash into the common folder.
2026-04-26 - Modified to test some ram chips off an A501 trap door card. Found 2 bad ram ic's.
2026-05-02 - Updated to use vga111.c from the common folder.
2026-05-03 - Added The mcp23s17 spi GPIO Expander to the common library.
2026-05-03 - Removed Duplicate Project Files.
2026-05-09 - Removed Old Code.
2026-05-23 - Added Project Framework for MCP951X Real Time Clock.
2026-05-24 - Reading and writing the RTC registers now works.
2026-05-24 - Moved The RTC Initialisation code into Common.
2026-05-24 - Added functions to get and set the time.
2026-05-25 - Added Date Functions.
2026-05-25 - Added Code To Dump All 3 Memory Areas Of The RTC IC.
2026-05-25 - Added functions for writing to the RTC EEPROM and protected EEPROM.
2026-05-27 - Added RTC_GetFlags() to allow more RTC state info to be displayed.
2026-05-28 - Added RTC Functions To Output A Square Wave And Control The Oscillator Trim Settings.
2026-05-28 - Added RTC Clear SRAM Command.
2026-05-30 - Added RTC_BatteryEnable. - Fixed Inverted AM/PM Flag. - Refactored Main Register Struct For Upcoming Functionality.
2026-05-30 - Added Code To Diplay The Power Up / Down Timestamps.
2026-05-30 - Updated Crystal Load Capacitance Value, 10pf may still be a bit low.
2026-05-30 - MSM6242 is connected to the rp2350 and i can see the seconds register counting.
2026-05-31 - Added code to read and display the time.
2026-06-01 - Code is now reliably reading the date and time from the MSM6242B RTC.
2026-06-01 - Clean up and display control registers.
2026-06-03 - Added Schematic For Connection Of MSM6242B To My RP2350B Prototype Board.
2026-06-03 - Removed Toggling Of The CS Line From Read And Write - Fixed Error Text Displaying The Incorrect String.
